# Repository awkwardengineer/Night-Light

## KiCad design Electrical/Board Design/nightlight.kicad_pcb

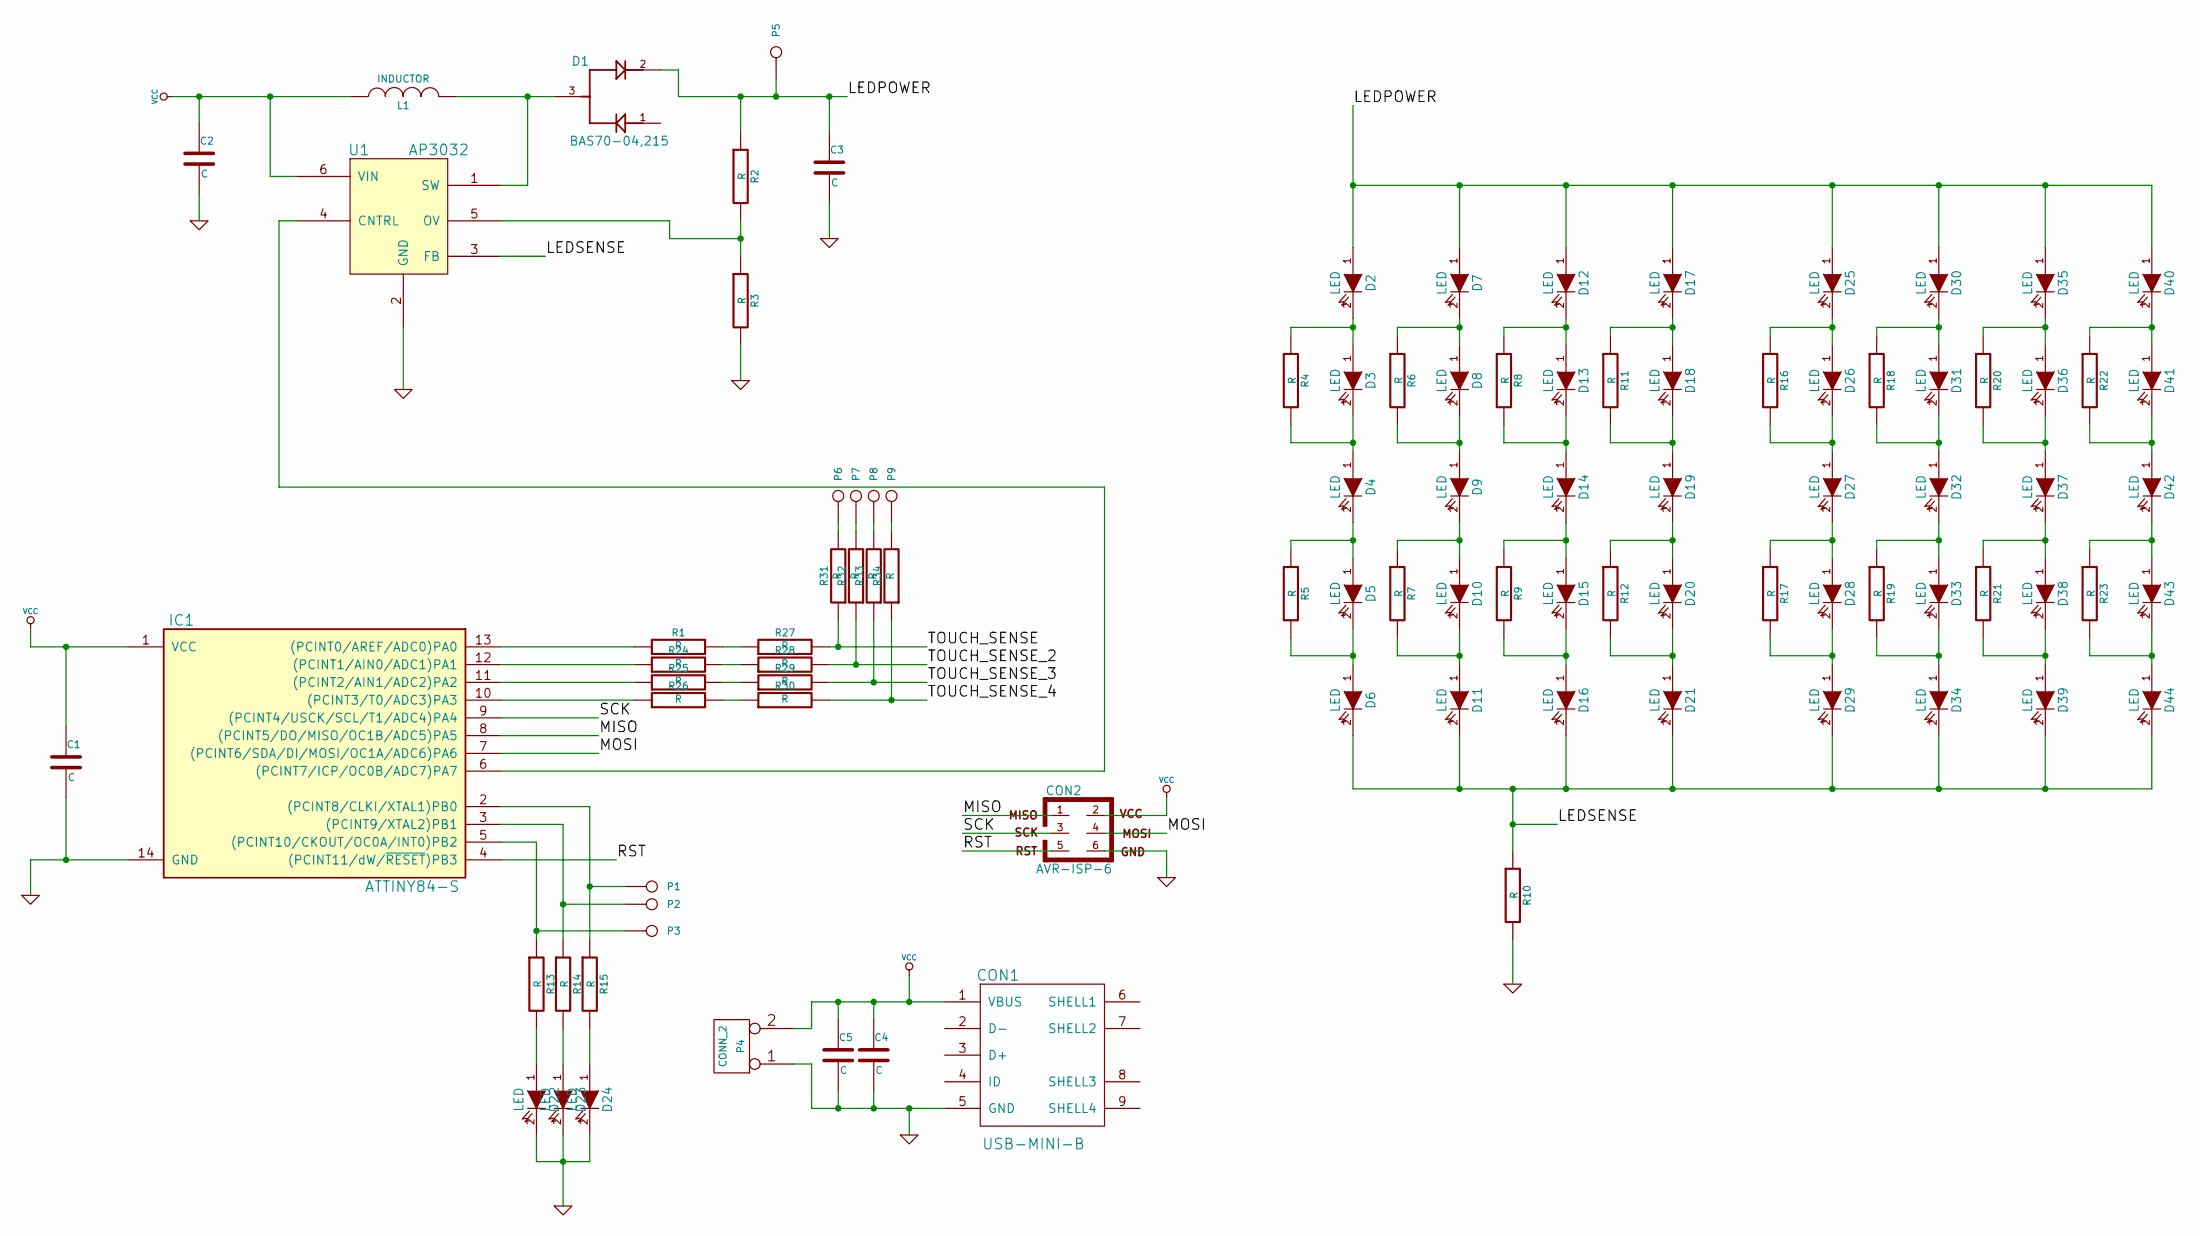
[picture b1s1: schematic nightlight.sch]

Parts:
C1, C2, C3, C4, C5: C
CON1: USB-MINI-B
CON2: AVR-ISP-6
D1: BAS70-04,215; SOT23
D2, D3, D4, D5, D6, D7, D8, D9, D10, D11, D12, D13, D14, D15, D16, D17, D18, D19, D20, D21, D22, D23, D24, D25, D26, D27, D28, D29, D30, D31, D32, D33, D34, D35, D36, D37, D38, D39, D40, D41, D42, D43, D44: LED
IC1: ATTINY84-S; SO14
L1: INDUCTOR
P1, P2, P3, P5, P6, P7, P8, P9: CONN_1
P4: CONN_2
R1, R2, R3, R4, R5, R6, R7, R8, R9, R10, R11, R12, R13, R14, R15, R16, R17, R18, R19, R20, R21, R22, R23, R24, R25, R26, R27, R28, R29, R30, R31, R32, R33, R34: R
U1: AP3032

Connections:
/LEDPOWER: C3.1, D1.2, D2.1 (A), D7.1 (A), D12.1 (A), D17.1 (A), D25.1 (A), D30.1 (A), D35.1 (A), D40.1 (A), P5.1, R2.1
/LEDSENSE: D6.2 (K), D11.2 (K), D16.2 (K), D21.2 (K), D29.2 (K), D34.2 (K), D39.2 (K), D44.2 (K), R10.1, U1.3 (FB)
/MISO: CON2.1, IC1.8 ((PCINT5/DO/MISO/OC1B/ADC5)PA5)
/MOSI: CON2.4, IC1.7 ((PCINT6/SDA/DI/MOSI/OC1A/ADC6)PA6)
/RST: CON2.5, IC1.4 ((PCINT11/dW/~RESET~)PB3)
/SCK: CON2.3, IC1.9 ((PCINT4/USCK/SCL/T1/ADC4)PA4)
/TOUCH_SENSE: R27.2, R31.1
/TOUCH_SENSE_2: R28.2, R32.1
/TOUCH_SENSE_3: R29.2, R33.1
/TOUCH_SENSE_4: R30.2, R34.1
GND: C1.2, C2.2, C3.2, C4.2, C5.2, CON1.5 (GND), CON2.6, D22.2 (K), D23.2 (K), D24.2 (K), IC1.14 (GND), P4.1, R3.2, R10.2, U1.2 (GND)
unnamed: D25.2 (K), D26.1 (A), R16.1
unnamed: D27.2 (K), D28.1 (A), R17.1
unnamed: D28.2 (K), D29.1 (A), R17.2
unnamed: D26.2 (K), D27.1 (A), R16.2
unnamed: D40.2 (K), D41.1 (A), R22.1
unnamed: D41.2 (K), D42.1 (A), R22.2
unnamed: D42.2 (K), D43.1 (A), R23.1
unnamed: D37.2 (K), D38.1 (A), R21.1
unnamed: D38.2 (K), D39.1 (A), R21.2
unnamed: D35.2 (K), D36.1 (A), R20.1
unnamed: D36.2 (K), D37.1 (A), R20.2
unnamed: D31.2 (K), D32.1 (A), R18.2
unnamed: D30.2 (K), D31.1 (A), R18.1
unnamed: D33.2 (K), D34.1 (A), R19.2
unnamed: D32.2 (K), D33.1 (A), R19.1
unnamed: D24.1 (A), R15.2
unnamed: D22.1 (A), R13.2
unnamed: D23.1 (A), R14.2
unnamed: IC1.2 ((PCINT8/CLKI/XTAL1)PB0), P1.1, R15.1
unnamed: IC1.3 ((PCINT9/XTAL2)PB1), P2.1, R14.1
unnamed: IC1.5 ((PCINT10/CKOUT/OC0A/INT0)PB2), P3.1, R13.1
unnamed: P8.1, R33.2
unnamed: P7.1, R32.2
unnamed: P6.1, R31.2
unnamed: P9.1, R34.2
unnamed: D43.2 (K), D44.1 (A), R23.2
unnamed: R1.2, R27.1
unnamed: R24.2, R28.1
unnamed: R25.2, R29.1
unnamed: R26.2, R30.1
unnamed: IC1.10 ((PCINT3/T0/ADC3)PA3), R26.1
unnamed: IC1.11 ((PCINT2/AIN1/ADC2)PA2), R25.1
unnamed: IC1.12 ((PCINT1/AIN0/ADC1)PA1), R24.1
unnamed: R2.2, R3.1, U1.5 (OV)
unnamed: D19.2 (K), D20.1 (A), R12.1
unnamed: D17.2 (K), D18.1 (A), R11.1
unnamed: D18.2 (K), D19.1 (A), R11.2
unnamed: D20.2 (K), D21.1 (A), R12.2
unnamed: IC1.6 ((PCINT7/ICP/OC0B/ADC7)PA7), U1.4 (CNTRL)
unnamed: IC1.13 ((PCINT0/AREF/ADC0)PA0), R1.1
unnamed: D2.2 (K), D3.1 (A), R4.1
unnamed: D3.2 (K), D4.1 (A), R4.2
unnamed: D12.2 (K), D13.1 (A), R8.1
unnamed: D13.2 (K), D14.1 (A), R8.2
unnamed: D14.2 (K), D15.1 (A), R9.1
unnamed: D15.2 (K), D16.1 (A), R9.2
unnamed: D5.2 (K), D6.1 (A), R5.2
unnamed: D1.3, L1.2, U1.1 (SW)
unnamed: D4.2 (K), D5.1 (A), R5.1
unnamed: D8.2 (K), D9.1 (A), R6.2
unnamed: D7.2 (K), D8.1 (A), R6.1
unnamed: D10.2 (K), D11.1 (A), R7.2
unnamed: D9.2 (K), D10.1 (A), R7.1
VCC: C1.1, C2.1, C4.1, C5.1, CON1.1 (VBUS), CON2.2, IC1.1 (VCC), L1.1, P4.2 (PM), U1.6 (VIN)

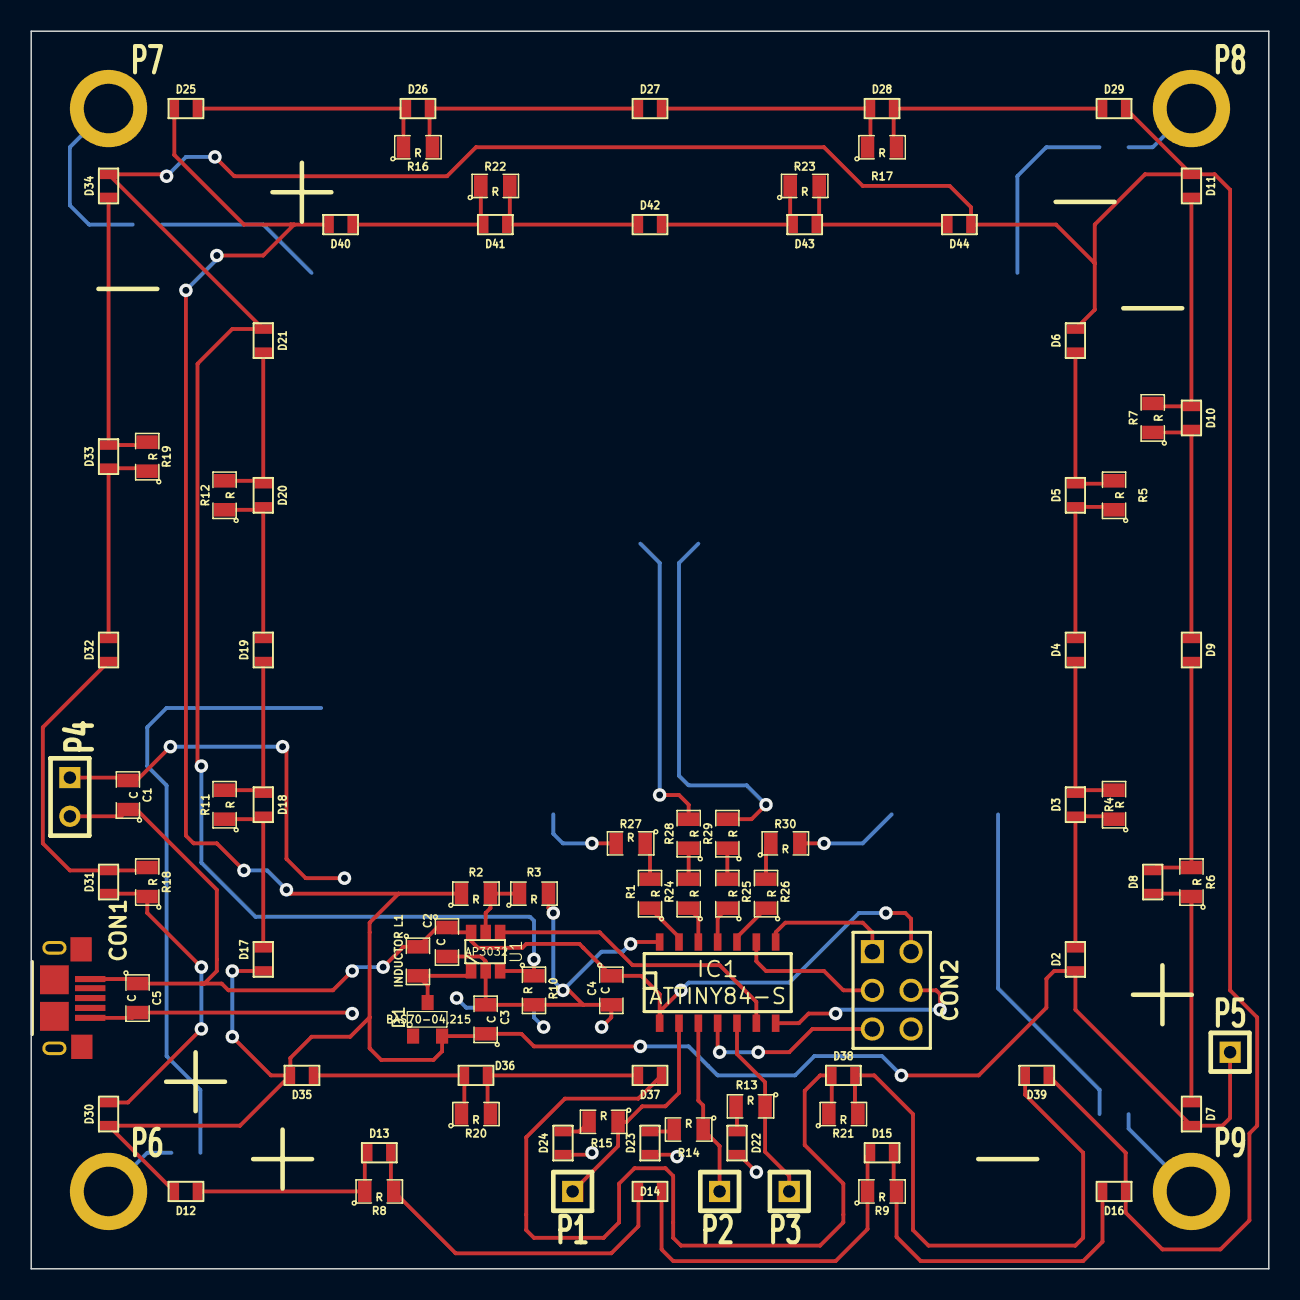
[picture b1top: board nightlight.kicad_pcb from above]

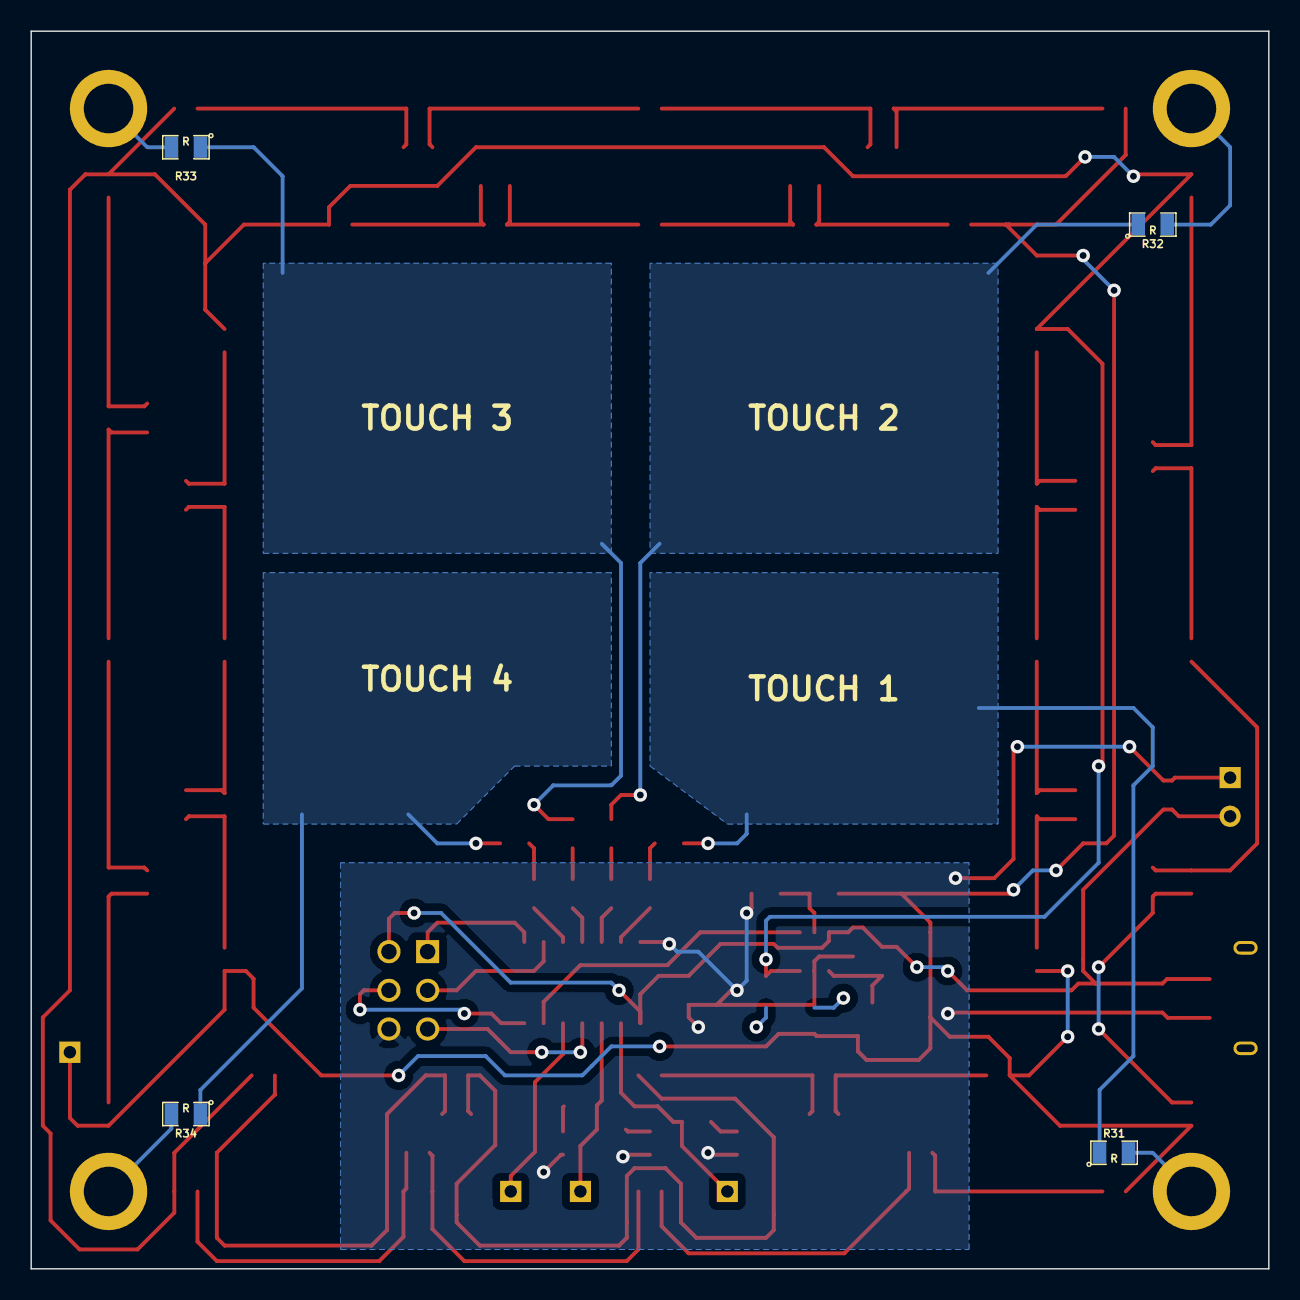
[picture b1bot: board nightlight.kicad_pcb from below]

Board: 2 copper layers, 81.3 x 81.3 mm, 97 parts (4 on the bottom side), 65 nets.

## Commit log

2015-10-13 :tada: Added .gitattributes & .gitignore files
2015-10-13 initial creation
